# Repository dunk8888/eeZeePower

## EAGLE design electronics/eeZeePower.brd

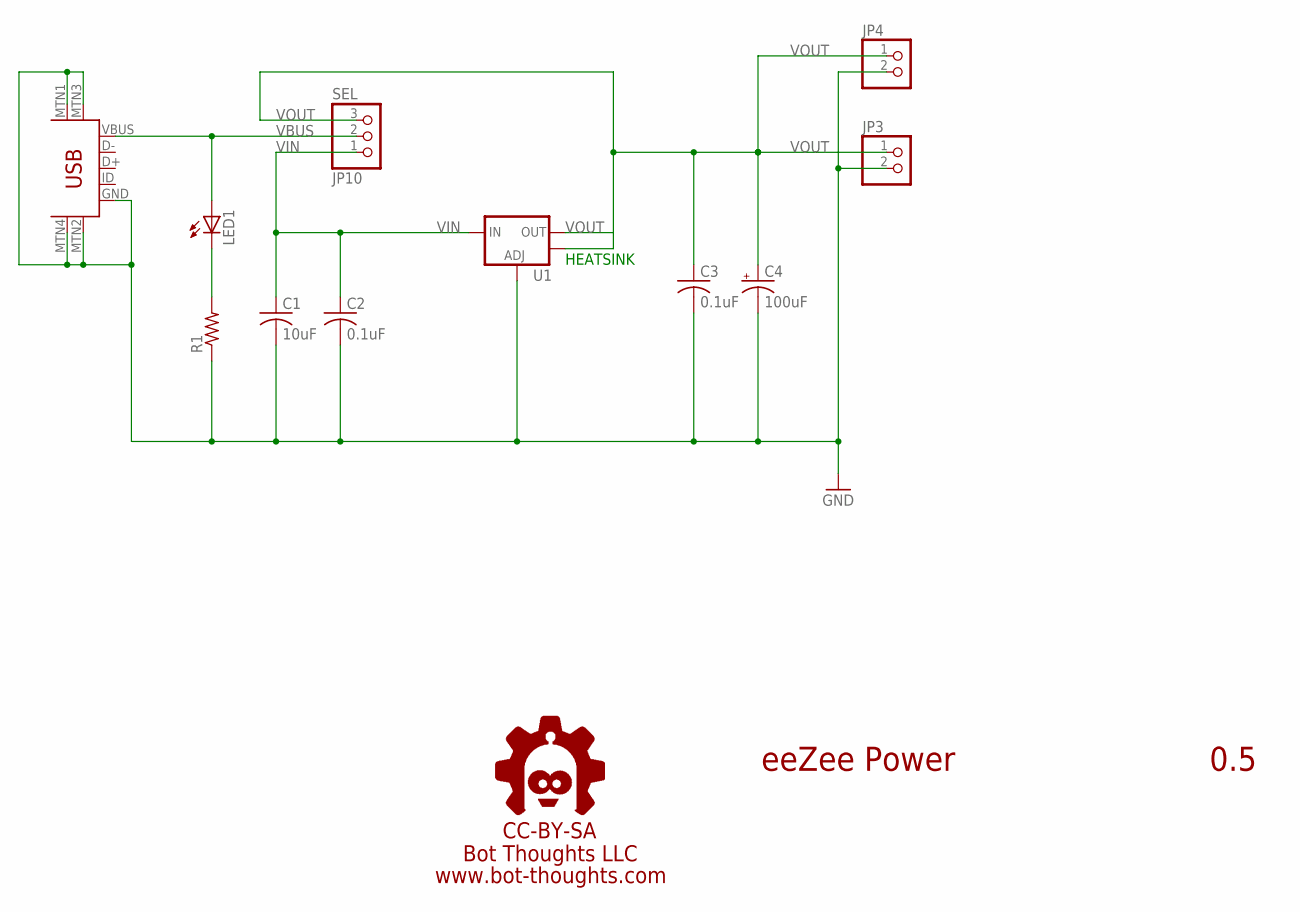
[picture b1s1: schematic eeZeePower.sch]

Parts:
C1: 10uF; C1206
C2, C3: 0.1uF; C0603
C4: 100uF; SMC_B
JP3, JP4: PINHD-1X02_2.54-S; 1X02-S
JP10: SEL; 1X03-S
LED1: LEDCHIPLED_1206; CHIPLED_1206
R1: R-US_R0603; R0603
U1: V_REG_LM1117SOT223; SOT223
U$1: USB-MINIB-5PIN; USB-MINIB
U$3: BOT-THOUGHTS-LOGO-MD; BTLOGOM

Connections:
GND: C1.2, C2.2, C3.2, C4.-, JP3.2, JP4.2, R1.1, U1.1 (ADJ), U$1.GND, U$1.MTN1 (MTN2), U$1.MTN2 (MTN3), U$1.MTN3 (MTN1), U$1.MTN4
unnamed: LED1.C, R1.2
VBUS: JP10.2, LED1.A, U$1.VBUS
VIN: C1.1, C2.1, JP10.1, U1.3 (IN)
VOUT: C3.1, C4.+, JP3.1, JP4.1, JP10.3, U1.2 (OUT), U1.4 (OUT)

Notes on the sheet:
eeZee Power
0.5
HEATSINK

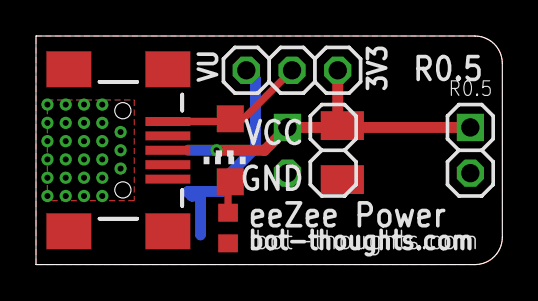
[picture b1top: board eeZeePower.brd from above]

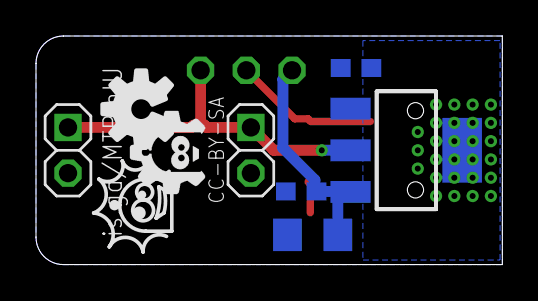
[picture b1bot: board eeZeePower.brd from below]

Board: 2 copper layers, 25.9 x 12.7 mm, 12 parts (7 on the bottom side), 5 nets.

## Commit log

2014-10-17 Switched to TC1262 regulator, improved thermal design, moved jumper and LED around.
2015-04-30 changed file permissions
2015-08-05 Moved electronics files into subdir, created documentation directory and added assembly instructions
2015-08-05 added assembly guide
2015-08-05 moved electronics into subdirectory
2015-08-05 Changed permissions on electronics files
2015-11-25 converted to micro-B connector, shrunk board, changed layout to fit, modded silk slightly, removed 0.1uF output cap
2015-11-25 updated gerbers
2015-11-25 updated zip
2015-11-25 added mu-B indicator on silk
2015-11-25 added gitignore
2015-12-04 updated microb footprint with new library version, added shielding to ground, fixed missing junction
2015-12-04 added value to resistor, removed silk value
2015-12-04 moved silkscreen
2015-12-04 updated microb after fixing silk in package
2015-12-04 Updated version #
2015-12-04 updated silk, updated board name to microB
2015-12-04 updated zip, gerbers
2016-01-27 replaced logo and document field.
2016-01-27 replaced logo, moved power pin headers, changed layout of passives, added help url
2016-01-27 revised logo
2016-01-27 modified logo to polygons, arcs; minor tweaks, moved url
2016-01-27 updated logo
2016-01-27 updated gerbers, zip
2016-01-28 Converted documentation to markdown, created full user guide
2016-01-28 added images to user guide
2016-01-28 updated specs

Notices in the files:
electronics/eeZeePower.brd:
CC-BY-SA
parts and their libraries:
SparkFun: Licensing: CC v3.0 Share-Alike You are welcome to use this library for commercial purposes.
